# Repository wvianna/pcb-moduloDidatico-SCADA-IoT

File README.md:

# Projeto: PCB Módulo Didático SCADA/IoT

## Descrição do Projeto
Este projeto tem como objetivo fornecer uma plataforma de aprendizado para estudantes e entusiastas de automação industrial, sistemas SCADA e Internet das Coisas (IoT). A placa de circuito impresso (PCB) foi projetada para ser utilizada em laboratórios educacionais, permitindo a prática de conceitos teóricos em um ambiente controlado.

A PCB integra um **NodeMCU v2 (ESP8266)** com os seguintes componentes onboard:

- **Potenciômetro** — sinal analógico variável (simula sensor analógico)
- **Sensor DS18B20** — temperatura digital via 1-Wire
- **Driver de potência (transistor/resistência de aquecimento)** — carga controlada por PWM
- **Driver para servomotores** — canais PWM para azimute e elevação
- **Interface RS485 (MAX485)** — comunicação serial industrial half-duplex
- **Conectores para coils** — saídas digitais para relés ou buzzer
- **Conectores para entradas digitais** — contato seco ou switch onboard
- **LEDs de sinalização** — indicação visual de estado

---

> 🧩 **Projeto do firmware:** Este projeto foi desenvolvido para o firmware disponível em [github.com/wvianna/pcb-moduloDidatico-SCADA-IoT-firmware](https://github.com/wvianna/pcb-moduloDidatico-SCADA-IoT-firmware). O firmware gerencia todos os I/Os, sensores e interface RS485, implementando comunicação via **Modbus TCP/RTU**, **MQTT** e **OPC UA PubSub** — com seleção de protocolo via interface web.

---

**Autor:** William da Silva Vianna  
**Software Utilizado:** KiCad (v9 ou superior)

---

## 🧠 Visão Geral da Arquitetura

```mermaid
flowchart LR
  subgraph PCB["Placa PCB (Hardware)"]
    direction TB
    NODE[NodeMCU ESP8266]
    SEN[Sensores<br/>ADC + DS18B20]
    ATU[Atuadores<br/>Coils + PWM + Resistência]
    RS[RS485 MAX485]
    IN[Entradas Digitais]
  end

  subgraph FW["Firmware (software)"]
    REG[Modelo Interno<br/>de Registradores]
    PROT[Protocolo Ativo<br/>Modbus / MQTT / OPC UA]
    WEB[Servidor Web<br/>de Configuração]
  end

  subgraph EXT["Mundo Externo"]
    SCADA[SCADA / IHM]
    BRK[Broker MQTT]
    NRED[Node-RED]
  end

  NODE --> REG
  SEN --> REG
  REG --> ATU
  REG --> IN
  REG --> PROT
  WEB --> REG
  PROT --> SCADA
  PROT --> BRK
  PROT --> NRED
  RS -.-> SCADA
```

---

## � Pinout do NodeMCU

A imagem abaixo mostra a numeração dos pinos do **NodeMCU v2 (ESP8266)** utilizada no projeto. 

---

## �📋 Mapeamento de I/Os Físicos

A tabela abaixo relaciona cada funcionalidade da PCB ao pino do NodeMCU e ao registro Modbus correspondente. Este mapeamento é idêntico para todos os protocolos (Modbus, MQTT e OPC UA).

### Saídas Discretas (Coils)

| Endereço Modbus | Função | Pino NodeMCU | GPIO | Componente na PCB |
| ---: | --- | --- | --- | --- |
| 00001 | Saída discreta 1 | D0 | GPIO16 | Conector para relé/buzzer |
| 00002 | Saída discreta 2 | TX | GPIO1 | Conector para relé/buzzer |

### Entradas Discretas (Discrete Inputs)

| Endereço Modbus | Função | Pino NodeMCU | GPIO | Componente na PCB |
| ---: | --- | --- | --- | --- |
| 10001 | Entrada discreta 1 | D8 | GPIO15 | Switch onboard ou contato seco externo |
| 10002 | Entrada discreta 2 | RX | GPIO3 | Switch onboard ou contato seco externo |

> **Nota:** A entrada discreta 1 (ED1 / D8) também funciona como *boot pin* para forçar o modo de setup — basta colocá-la em nível baixo e reiniciar a placa.

### Entradas Analógicas (Input Registers)

| Endereço Modbus | Função | Pino NodeMCU | Faixa | Componente na PCB |
| ---: | --- | --- | ---: | --- |
| 30001 | ADC (potenciômetro) | A0 | 0..1023 | Potenciômetro onboard |
| 30002 | DS18B20 (temperatura) | D2 / GPIO4 | 0..1250 (x10 °C) | Sensor DS18B20 onboard |

### Saídas PWM (Holding Registers)

| Endereço Modbus | Função | Pino NodeMCU | GPIO | Faixa | Componente na PCB |
| ---: | --- | --- | --- | ---: | --- |
| 40001 | PWM azimute | D7 | GPIO13 | 0..1023 | Driver para servomotor |
| 40002 | PWM elevação | D3 | GPIO0 | 0..1023 | Driver para servomotor |
| 40003 | PWM resistência de aquecimento | D1 | GPIO5 | 0..1023 | Transistor + resistor de aquecimento onboard |

### Interface RS485 (Modbus RTU)

| Sinal MAX485 | Pino NodeMCU | GPIO |
| --- | --- | --- |
| RO (receptor) | D5 | GPIO14 |
| DI (driver) | D6 | GPIO12 |
| DE + RE (direção) | D4 | GPIO2 |

---
TIPO       |     DEVICE     | RANGE  |MODBUS
SD1        |BUZZER - PONTE H| 0 1    |COIL 00001
SD2        |RELE - PONTE H  | 0 1    |COIL 00002
PWM1       |SERVO - AZIMUTE | 0~1023 |H.R. 40001
PWM2       |SERVO - ELEVAÇÃO| 0~1023 |H.R. 40002
PMW3       |RESISTÊNCIA     | 0~1023 |H.R. 40003
ED1        |SW SECO - SETUP | 0 1    |D.I. 10001
ED2        |SW SECO         | 0 1    |D.I. 10002
EA0        |POTENCIÔMETRO   | 0~1023 |I.R. 30001
TEMPERATURA|DS18B20         | oC X 10|I.R. 30002
---

## 🔌 Diagrama de Blocos da PCB

```mermaid
flowchart TD
  subgraph PCB["PCB Módulo Didático SCADA/IoT"]
    MCU[NodeMCU ESP8266]

    subgraph ENTRADAS["Entradas"]
      POTE[Potenciômetro<br/>A0 / ADC]
      DS18[DS18B20<br/>D2 / 1-Wire]
      SW1[Switch ED1<br/>D8 / GPIO15]
      SW2[Switch ED2<br/>RX / GPIO3]
    end

    subgraph SAIDAS["Saídas"]
      C1[Coil 1<br/>D0 / GPIO16]
      C2[Coil 2<br/>TX / GPIO1]
      SRV1[Servo Azimute<br/>D7 / PWM]
      SRV2[Servo Elevação<br/>D3 / PWM]
      AQUE[Resistência<br/>D1 / PWM]
    end

    subgraph COMUM["Comunicação"]
      RS485[MAX485<br/>RS485 Half-Duplex]
    end

    subgraph SINAL["Sinalização"]
      LED[LED Config<br/>D4 / GPIO2]
    end

    MCU --- ENTRADAS
    MCU --- SAIDAS
    MCU --- RS485
    MCU --- SINAL
  end
```

---

## ⚡ Especificações Elétricas

| Parâmetro | Valor |
| --- | --- |
| Alimentação da placa | 5V DC (via USB ou conector) |
| Regulador onboard | 3,3V para o NodeMCU |
| Nível lógico dos GPIOs | 3,3V |
| Corrente máxima por GPIO | ~12 mA (com resistor de limitação) |
| Tensão no barramento RS485 | Diferencial (A/B) |
| Temperatura do DS18B20 | -55°C a +125°C |
| Faixa do ADC | 0..3,3V (10 bits, 0..1023) |

---

## 💻 Necessidade de Firmware

> ⚠️ **Nota Importante:** Este hardware **não é puramente analógico**. A placa foi projetada ao redor de uma arquitetura programável — o circuito impresso isolado não desempenha nenhuma função sem o respectivo **firmware**.

O firmware disponível em [pcb-moduloDidatico-SCADA-IoT-firmware](https://github.com/wvianna/pcb-moduloDidatico-SCADA-IoT-firmware) implementa:

1. **Inicialização (Setup):** Configuração dos registradores, direção dos pinos de I/O e taxas de transmissão dos barramentos.
2. **Loop principal cooperativo:** Leitura cíclica de sensores, atualização do modelo interno de registradores e aplicação nas saídas físicas — sem uso de `delay()` bloqueante.
3. **Servidor web de configuração:** Interface para definir SSID, IP, protocolo ativo (Modbus/MQTT/OPC UA) e parâmetros de comunicação, acessível via modo AP.
4. **Pilhas de comunicação:** Modbus TCP (porta 502), Modbus RTU (RS485), MQTT (PubSubClient) e OPC UA PubSub sobre MQTT.
5. **Persistência em LittleFS:** Configuração salva em arquivo texto na flash, com validação e fallback para valores padrão.

---

## 📁 Estrutura de Arquivos no Repositório

```text
├── esquema.pdf             # Diagrama esquemático exportado para leitura
├── meu-projeto.kicad_pro   # Arquivo de gerenciamento do projeto KiCad
├── meu-projeto.kicad_sch   # Folha do desenho esquemático
├── meu-projeto.kicad_pcb   # Layout da placa de circuito impresso
├── docs/
│   ├── mapeamentopinosmb.txt  # Mapa de pinos em formato CSV
│   └── requisitos.txt         # Requisitos elétricos e funcionais
├── firmware/                  # Submódulo do firmware
└── .gitignore              # Filtro de arquivos temporários do KiCad
```

---

## 🔗 Links Relacionados

| Recurso | Link |
| --- | --- |
| Repositório do firmware | [github.com/wvianna/pcb-moduloDidatico-SCADA-IoT-firmware](https://github.com/wvianna/pcb-moduloDidatico-SCADA-IoT-firmware) |
| Documentação do firmware | README do firmware |
| Esquema elétrico | `esquema.pdf` neste repositório |
| Mapa de pinos (CSV) | `docs/mapeamentopinosmb.txt` |

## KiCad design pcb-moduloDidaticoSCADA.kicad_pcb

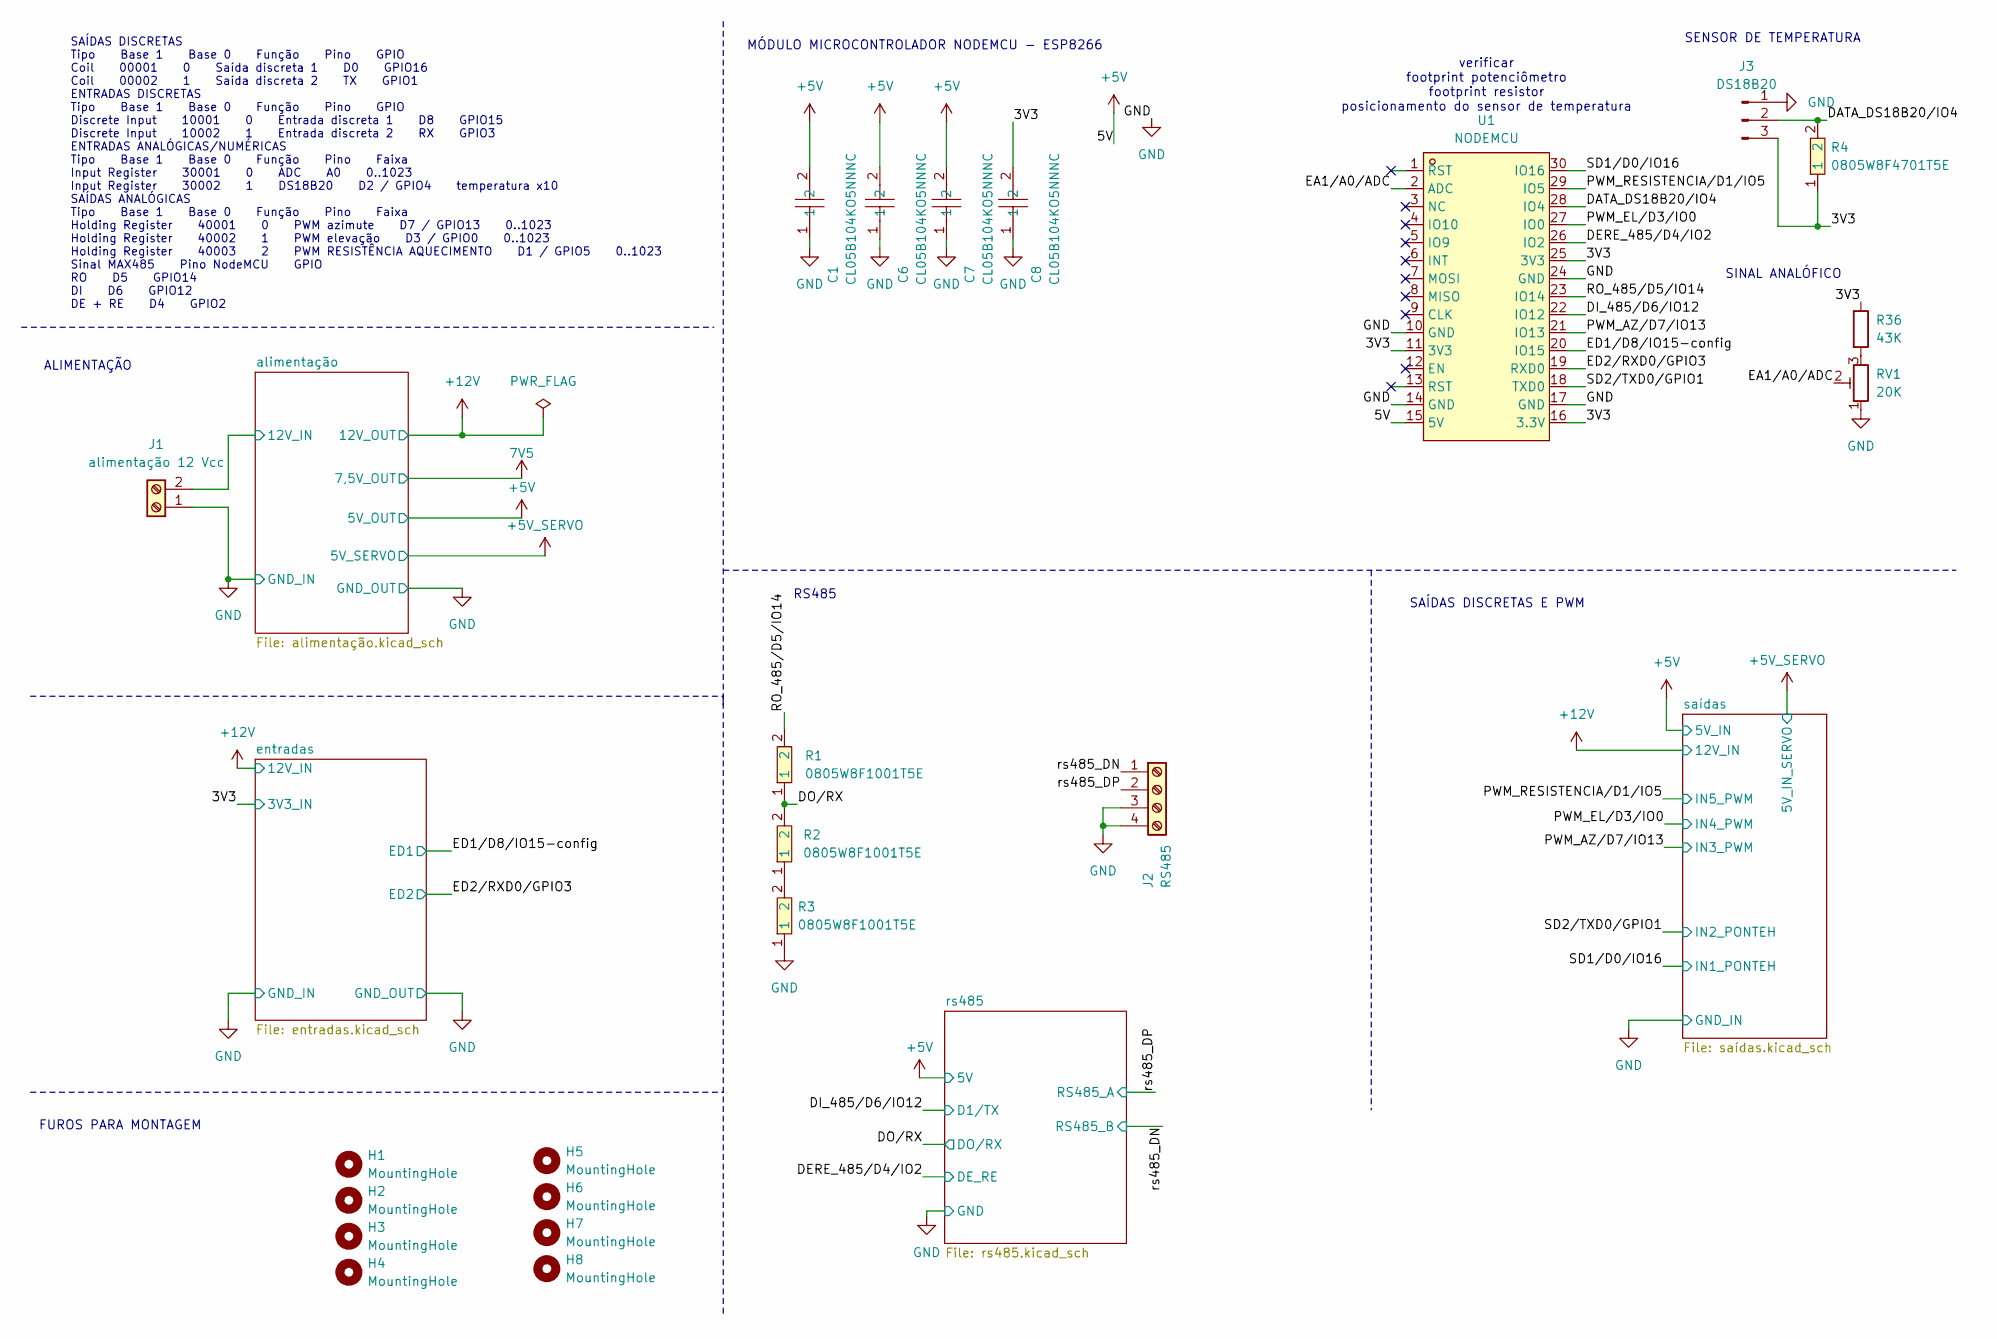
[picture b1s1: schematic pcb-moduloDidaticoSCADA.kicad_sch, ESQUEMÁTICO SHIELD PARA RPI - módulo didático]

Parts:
C1, C6, C7, C8: CL05B104KO5NNNC; C0402; MPN CL05B104KO5NNNC; LCSC Part C1525
H1, H2, H3, H4, H5, H6, H7, H8: MountingHole; MountingHole_3.2mm_M3
J1: alimentação 12 Vcc; TerminalBlock_MaiXu_MX126-5.0-02P_1x02_P5.00mm
J2: RS485; TerminalBlock_MetzConnect_Type101_RT01604HBWC_1x04_P5.08mm_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
J3: DS18B20; PinSocket_1x03_P2.54mm_Vertical
R1, R2, R3: 0805W8F1001T5E; R0805; MPN 0805W8F1001T5E; LCSC Part C17513
R4: 0805W8F4701T5E; R0805; LCSC Part C17673
R36: 43K; R_0805_2012Metric_Pad1.20x1.40mm_HandSolder
RV1: 20K; Potentiometer_Alpha_RD901F-40-00D_Single_Vertical
U1: NODEMCU; COMM-TH_NODEMCU-12F; MPN NODEMCU(12F); LCSC Part C2764098

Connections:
+5V: C1.2, C6.2, C7.2, U1.15 (5V); also elsewhere on the board
+12V: J1.2; also elsewhere on the board
/3V3: C8.2, J3.3, R4.1, R36.1, U1.11 (3V3), U1.16 (3.3V), U1.25 (3V3); also elsewhere on the board
/DATA_DS18B20/IO4: J3.2, R4.2, U1.28 (IO4)
/DERE_485/D4/IO2: U1.26 (IO2); also elsewhere on the board
/DI_485/D6/IO12: U1.22 (IO12); also elsewhere on the board
/DO/RX: R1.1, R2.2; also elsewhere on the board
/EA1/A0/ADC: RV1.2, U1.2 (ADC)
/ED1/D8/IO15-config: U1.20 (IO15); also elsewhere on the board
/ED2/RXD0/GPIO3: U1.19 (RXD0); also elsewhere on the board
/PWM_AZ/D7/IO13: U1.21 (IO13); also elsewhere on the board
/PWM_EL/D3/IO0: U1.27 (IO0); also elsewhere on the board
/PWM_RESISTENCIA/D1/IO5: U1.29 (IO5); also elsewhere on the board
/RO_485/D5/IO14: R1.2, U1.23 (IO14)
/SD1/D0/IO16: U1.30 (IO16); also elsewhere on the board
/SD2/TXD0/GPIO1: U1.18 (TXD0); also elsewhere on the board
/rs485_DN: J2.1; also elsewhere on the board
/rs485_DP: J2.2; also elsewhere on the board
GND: C1.1, C6.1, C7.1, C8.1, J1.1, J2.3, J2.4, J3.1, R3.1, RV1.1, U1.10 (GND), U1.14 (GND), U1.17 (GND), U1.24 (GND); also elsewhere on the board
unnamed: R2.1, R3.2
unnamed: R36.2, RV1.3

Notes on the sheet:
SENSOR DE TEMPERATURA
MÓDULO MICROCONTROLADOR NODEMCU - ESP8266
FUROS PARA MONTAGEM
SINAL ANALÓFICO
verificar footprint potenciômetro footprint resistor posicionamento do sensor de temperatura
ALIMENTAÇÃO
SAÍDAS DISCRETAS E PWM
RS485
SAÍDAS DISCRETAS Tipo Base 1 Base 0 Função Pino GPIO Coil 00001 0 Saída discreta 1 D0 GPIO16 Coil 00002 1 Saída discreta 2 TX GPIO1 ENTRADAS DISCRETAS Tipo Base 1 Base 0 Função Pino GPIO Discrete Input 10001 0 Entrada discreta 1 D8 GPIO15 Discrete Input 10002 1 Entrada discreta 2 RX GPIO3 ENTRADAS 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

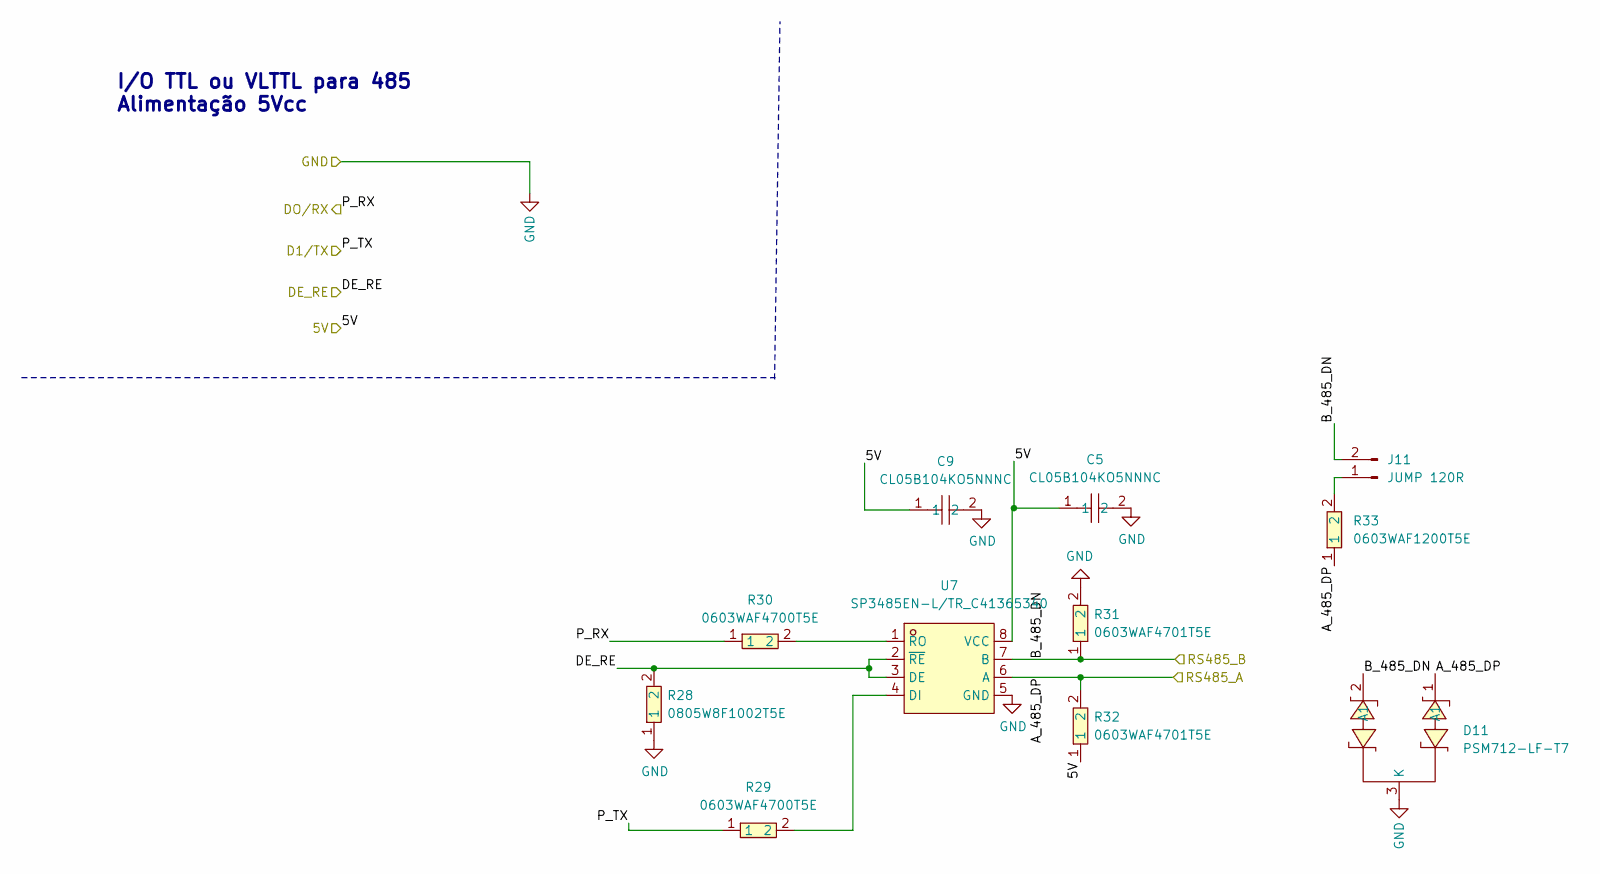
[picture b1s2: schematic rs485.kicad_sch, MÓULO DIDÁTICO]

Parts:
C5, C9: CL05B104KO5NNNC; C0402; MPN CL05B104KO5NNNC; LCSC Part C1525
D11: PSM712-LF-T7; SOT-23-3_L3.0-W1.7-P0.95-LS2.9-BR; MPN PSM712-LF-T7; LCSC Part C32677
J11: JUMP 120R; PinSocket_1x02_P2.54mm_Vertical
R28: 0805W8F1002T5E; R0805; MPN 0805W8F1002T5E; LCSC Part C17414
R29, R30: 0603WAF4700T5E; R0603; MPN 0603WAF4700T5E; LCSC Part C23179
R31, R32: 0603WAF4701T5E; R0603; MPN 0603WAF4701T5E; LCSC Part C23162
R33: 0603WAF1200T5E; R0603; MPN 0603WAF1200T5E; LCSC Part C22787
U7: SP3485EN-L/TR_C41365340; SO-8_L4.9-W3.9-P1.27-LS6.0-BL; MPN SP3485EN-L/TR; LCSC Part C41365340

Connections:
+5V: C5.1, C9.1, R32.1, U7.8 (VCC); also elsewhere on the board
/DERE_485/D4/IO2: R28.2, U7.2 (~RE), U7.3 (DE); also elsewhere on the board
/DI_485/D6/IO12: R29.1; also elsewhere on the board
/DO/RX: R30.1; also elsewhere on the board
/rs485_DN: D11.2 (A1), J11.2, R31.1, U7.7 (B); also elsewhere on the board
/rs485_DP: D11.1 (A1), R32.2, R33.1, U7.6 (A); also elsewhere on the board
GND: C5.2, C9.2, D11.3 (K), R28.1, R31.2, U7.5 (GND); also elsewhere on the board
unnamed: J11.1, R33.2
unnamed: R29.2, U7.4 (DI)
unnamed: R30.2, U7.1 (RO)

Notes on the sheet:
I/O TTL ou VLTTL para 485 Alimentação 5Vcc

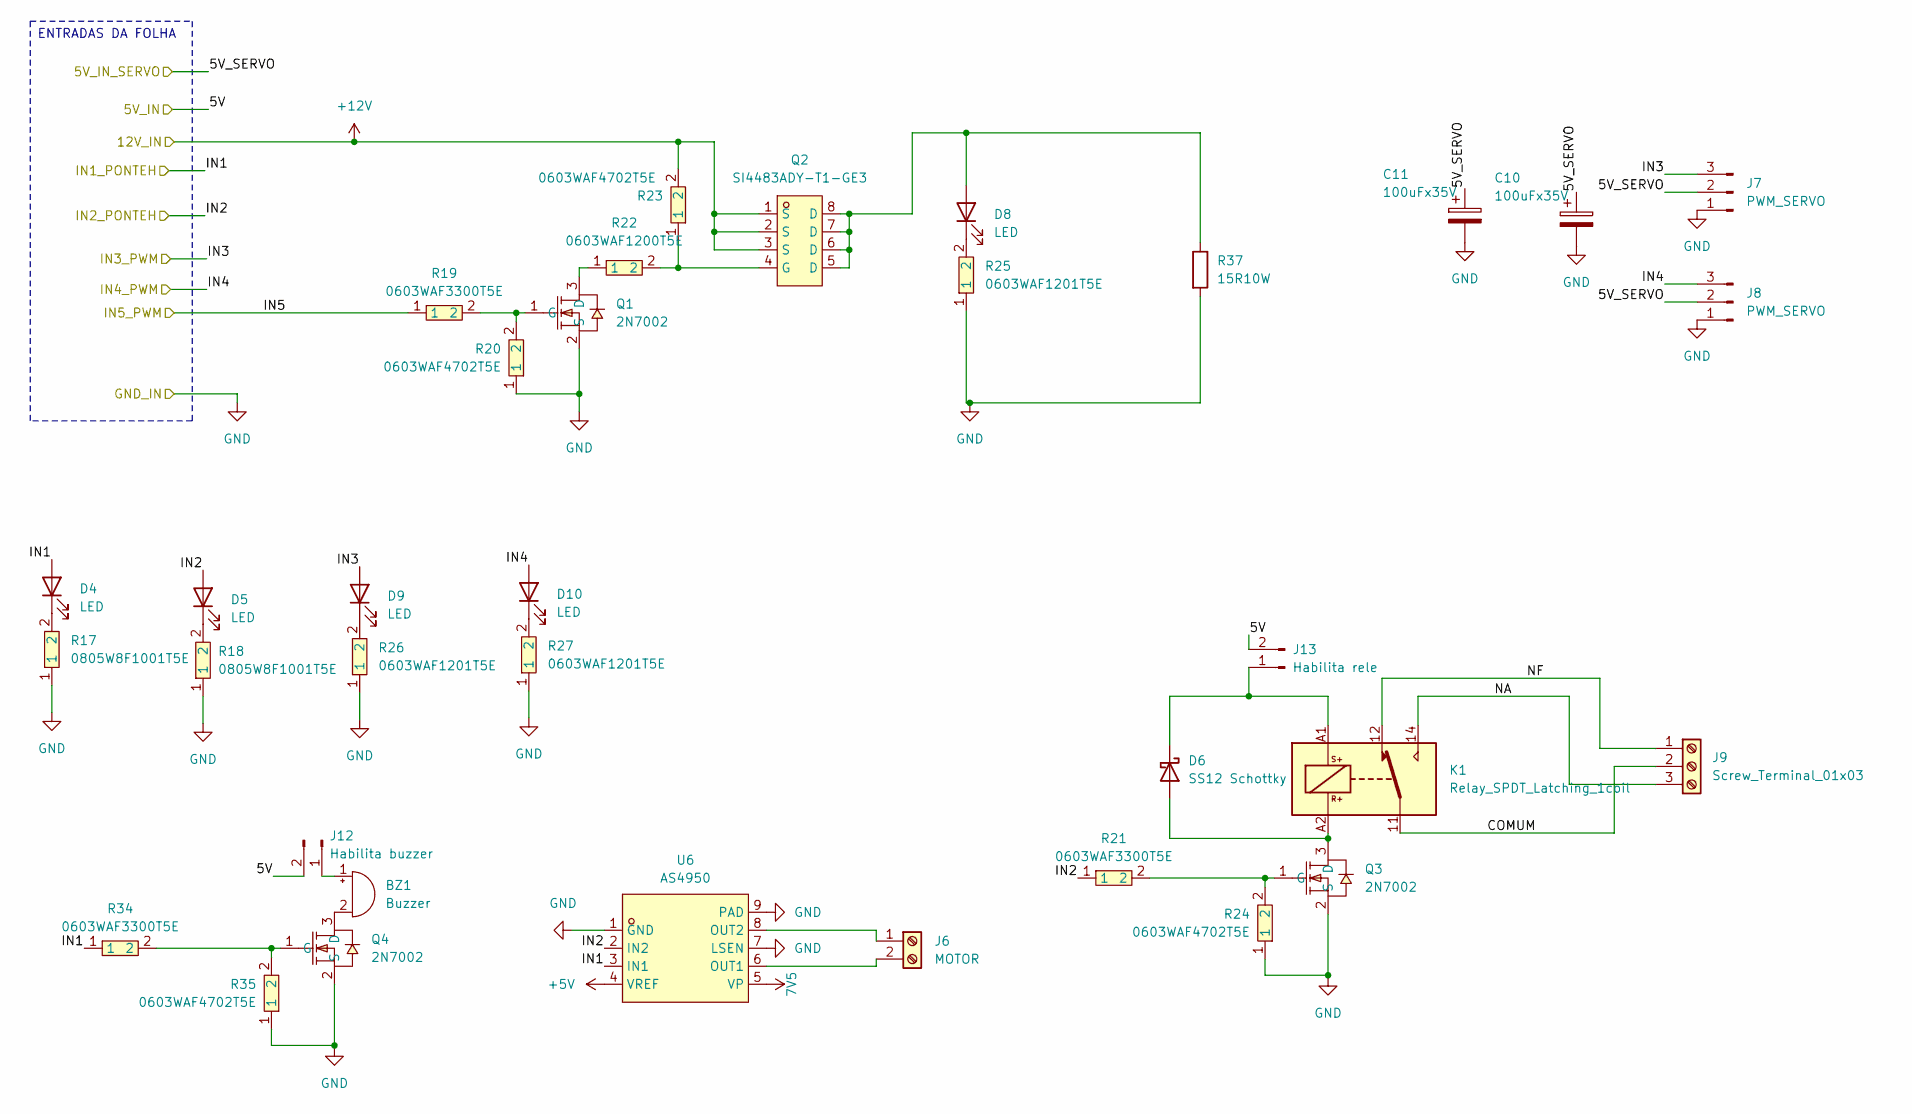
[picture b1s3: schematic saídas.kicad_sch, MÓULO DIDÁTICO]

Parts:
BZ1: Buzzer; Buzzer_12x9.5RM7.6
C10, C11: 100uFx35V; CP_Radial_D8.0mm_P3.50mm
D4, D5, D8, D9, D10: LED; LED_D5.0mm
D6: SS12 Schottky; D_SMA_Handsoldering
J6: MOTOR; TerminalBlock_MaiXu_MX126-5.0-02P_1x02_P5.00mm
J7, J8: PWM_SERVO; PinSocket_1x03_P2.54mm_Vertical
J9: Screw_Terminal_01x03; TerminalBlock_RND_205-00288_1x03_P5.08mm_Horizontal
J12: Habilita buzzer; PinSocket_1x02_P2.54mm_Vertical
J13: Habilita rele; PinSocket_1x02_P2.54mm_Vertical
K1: Relay_SPDT_Latching_1coil; Relay_SPDT_Finder_36.11
Q1, Q3, Q4: 2N7002; SOT-23-3_L2.9-W1.3-P1.90-LS2.4-BR; MPN 2N7002; LCSC Part C8545
Q2: SI4483ADY-T1-GE3; SO-8_L4.9-W3.9-P1.27-LS6.0-BL; LCSC Part C727843
R17, R18: 0805W8F1001T5E; R0805; MPN 0805W8F1001T5E; LCSC Part C17513
R19, R21, R34: 0603WAF3300T5E; R0603; MPN 0603WAF3300T5E; LCSC Part C23138
R20, R23, R24, R35: 0603WAF4702T5E; R0603; MPN 0603WAF4702T5E; LCSC Part C25819
R22: 0603WAF1200T5E; R0603; MPN 0603WAF1200T5E; LCSC Part C22787
R25, R26, R27: 0603WAF1201T5E; R0603; MPN 0603WAF1201T5E; LCSC Part C22765
R37: 15R10W; R_Axial_Power_L38.0mm_W9.0mm_P40.64mm
U6: AS4950; ESOP-8_L4.9-W3.9-P1.27-LS6.0-BL-EP; MPN AS4950; LCSC Part C2929412

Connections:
7V5: U6.5 (VP); also elsewhere on the board
+5V: J12.2, J13.2, U6.4 (VREF); also elsewhere on the board
+5V_SERVO: C10.1, C11.1, J7.2, J8.2; also elsewhere on the board
+12V: Q2.1 (S), Q2.2 (S), Q2.3 (S), R23.2; also elsewhere on the board
/PWM_AZ/D7/IO13: D9.2 (A), J7.3; also elsewhere on the board
/PWM_EL/D3/IO0: D10.2 (A), J8.3; also elsewhere on the board
/PWM_RESISTENCIA/D1/IO5: R19.1; also elsewhere on the board
/SD1/D0/IO16: D4.2 (A), R34.1, U6.3 (IN1); also elsewhere on the board
/SD2/TXD0/GPIO1: D5.2 (A), R21.1, U6.2 (IN2); also elsewhere on the board
/saídas/COMUM: J9.2, K1.11
/saídas/NA: J9.3, K1.14
/saídas/NF: J9.1, K1.12
GND: C10.2, C11.2, J7.1, J8.1, Q1.2 (S), Q3.2 (S), Q4.2 (S), R17.1, R18.1, R20.1, R24.1, R25.1, R26.1, R27.1, R35.1, R37.2, U6.1 (GND), U6.7 (LSEN), U6.9 (PAD); also elsewhere on the board
unnamed: BZ1.1 (+), J12.1
unnamed: BZ1.2 (-), Q4.3 (D)
unnamed: D4.1 (K), R17.2
unnamed: D5.1 (K), R18.2
unnamed: D6.2 (A), K1.A2, Q3.3 (D)
unnamed: D6.1 (K), J13.1, K1.A1
unnamed: D8.2 (A), Q2.5 (D), Q2.6 (D), Q2.7 (D), Q2.8 (D), R37.1
unnamed: D8.1 (K), R25.2
unnamed: D9.1 (K), R26.2
unnamed: D10.1 (K), R27.2
unnamed: J6.1, U6.8 (OUT2)
unnamed: J6.2, U6.6 (OUT1)
unnamed: Q1.3 (D), R22.1
unnamed: Q1.1 (G), R19.2, R20.2
unnamed: Q2.4 (G), R22.2, R23.1
unnamed: Q3.1 (G), R21.2, R24.2
unnamed: Q4.1 (G), R34.2, R35.2

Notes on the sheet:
ENTRADAS DA FOLHA

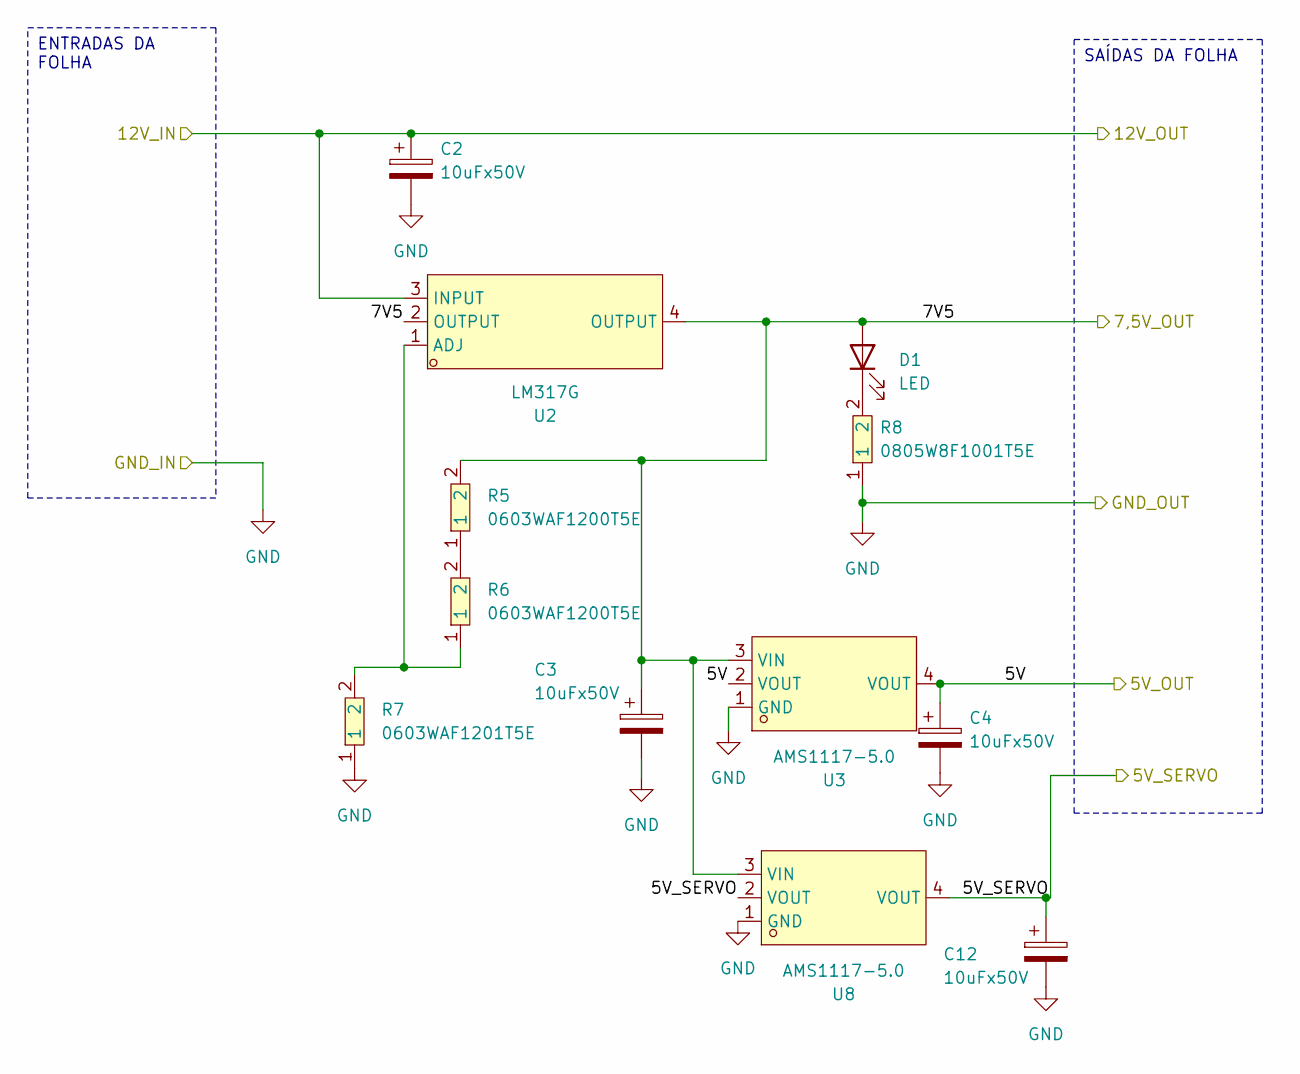
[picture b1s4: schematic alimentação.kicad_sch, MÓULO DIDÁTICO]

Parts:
C2, C3, C4, C12: 10uFx50V; CP_Radial_D5.0mm_P2.50mm
D1: LED; LED_D5.0mm
R5, R6: 0603WAF1200T5E; R0603; MPN 0603WAF1200T5E; LCSC Part C22787
R7: 0603WAF1201T5E; R0603; MPN 0603WAF1201T5E; LCSC Part C22765
R8: 0805W8F1001T5E; R0805; MPN 0805W8F1001T5E; LCSC Part C17513
U2: LM317G; SOT-223_L6.5-W3.5-P2.30-LS7.0-BR; MPN LM317G; LCSC Part C347367
U3, U8: AMS1117-5.0; SOT-223_L6.5-W3.5-P2.30-LS7.0-BR; MPN AMS1117-5.0; LCSC Part C6187

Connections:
7V5: C3.1, D1.2 (A), R5.2, U2.2 (OUTPUT), U2.4 (OUTPUT), U3.3 (VIN), U8.3 (VIN); also elsewhere on the board
+5V: C4.1, U3.2 (VOUT), U3.4 (VOUT); also elsewhere on the board
+5V_SERVO: C12.1, U8.2 (VOUT), U8.4 (VOUT); also elsewhere on the board
+12V: C2.1, U2.3 (INPUT); also elsewhere on the board
GND: C2.2, C3.2, C4.2, C12.2, R7.1, R8.1, U3.1 (GND), U8.1 (GND); also elsewhere on the board
unnamed: D1.1 (K), R8.2
unnamed: R5.1, R6.2
unnamed: R6.1, R7.2, U2.1 (ADJ)

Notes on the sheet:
ENTRADAS DA FOLHA
SAÍDAS DA FOLHA

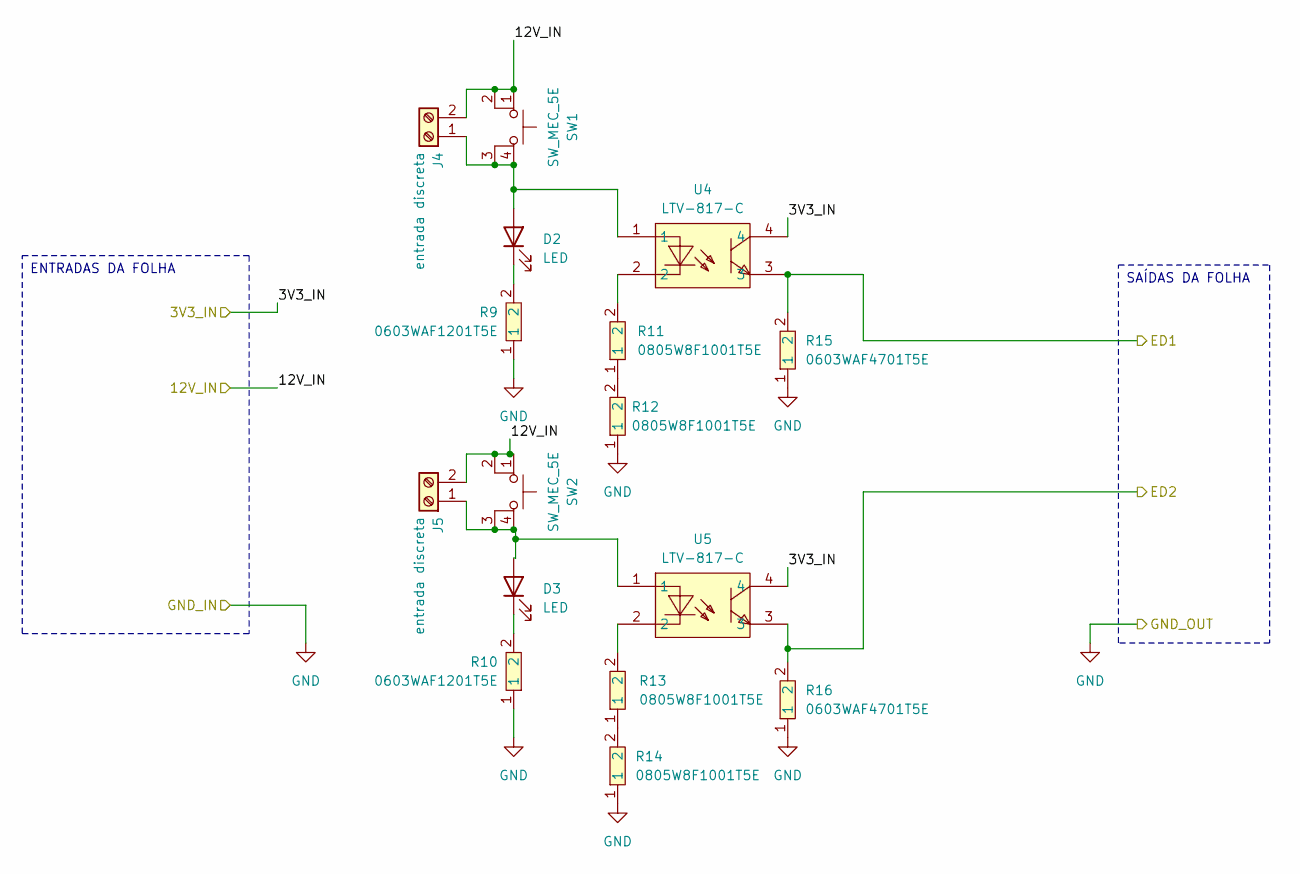
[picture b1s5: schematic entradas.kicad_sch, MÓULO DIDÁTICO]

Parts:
D2, D3: LED; LED_D5.0mm
J4, J5: entrada discreta; TerminalBlock_MaiXu_MX126-5.0-02P_1x02_P5.00mm
R9, R10: 0603WAF1201T5E; R0603; MPN 0603WAF1201T5E; LCSC Part C22765
R11, R12, R13, R14: 0805W8F1001T5E; R0805; MPN 0805W8F1001T5E; LCSC Part C17513
R15, R16: 0603WAF4701T5E; R0603; MPN 0603WAF4701T5E; LCSC Part C23162
SW1, SW2: SW_MEC_5E; SW_MEC_5GSH9
U4, U5: LTV-817-C; DIP-4_L4.6-W6.5-P2.54-LS7.6-BL

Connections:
+12V: J4.2, J5.2, SW1.1, SW1.2, SW2.1, SW2.2; also elsewhere on the board
/3V3: U4.4, U5.4; also elsewhere on the board
/ED1/D8/IO15-config: R15.2, U4.3; also elsewhere on the board
/ED2/RXD0/GPIO3: R16.2, U5.3; also elsewhere on the board
GND: R9.1, R10.1, R12.1, R14.1, R15.1, R16.1; also elsewhere on the board
unnamed: D2.2 (A), J4.1, SW1.3 (K), SW1.4 (A), U4.1
unnamed: D2.1 (K), R9.2
unnamed: D3.2 (A), J5.1, SW2.3 (K), SW2.4 (A), U5.1
unnamed: D3.1 (K), R10.2
unnamed: R11.1, R12.2
unnamed: R11.2, U4.2
unnamed: R13.1, R14.2
unnamed: R13.2, U5.2

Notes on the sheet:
ENTRADAS DA FOLHA
SAÍDAS DA FOLHA

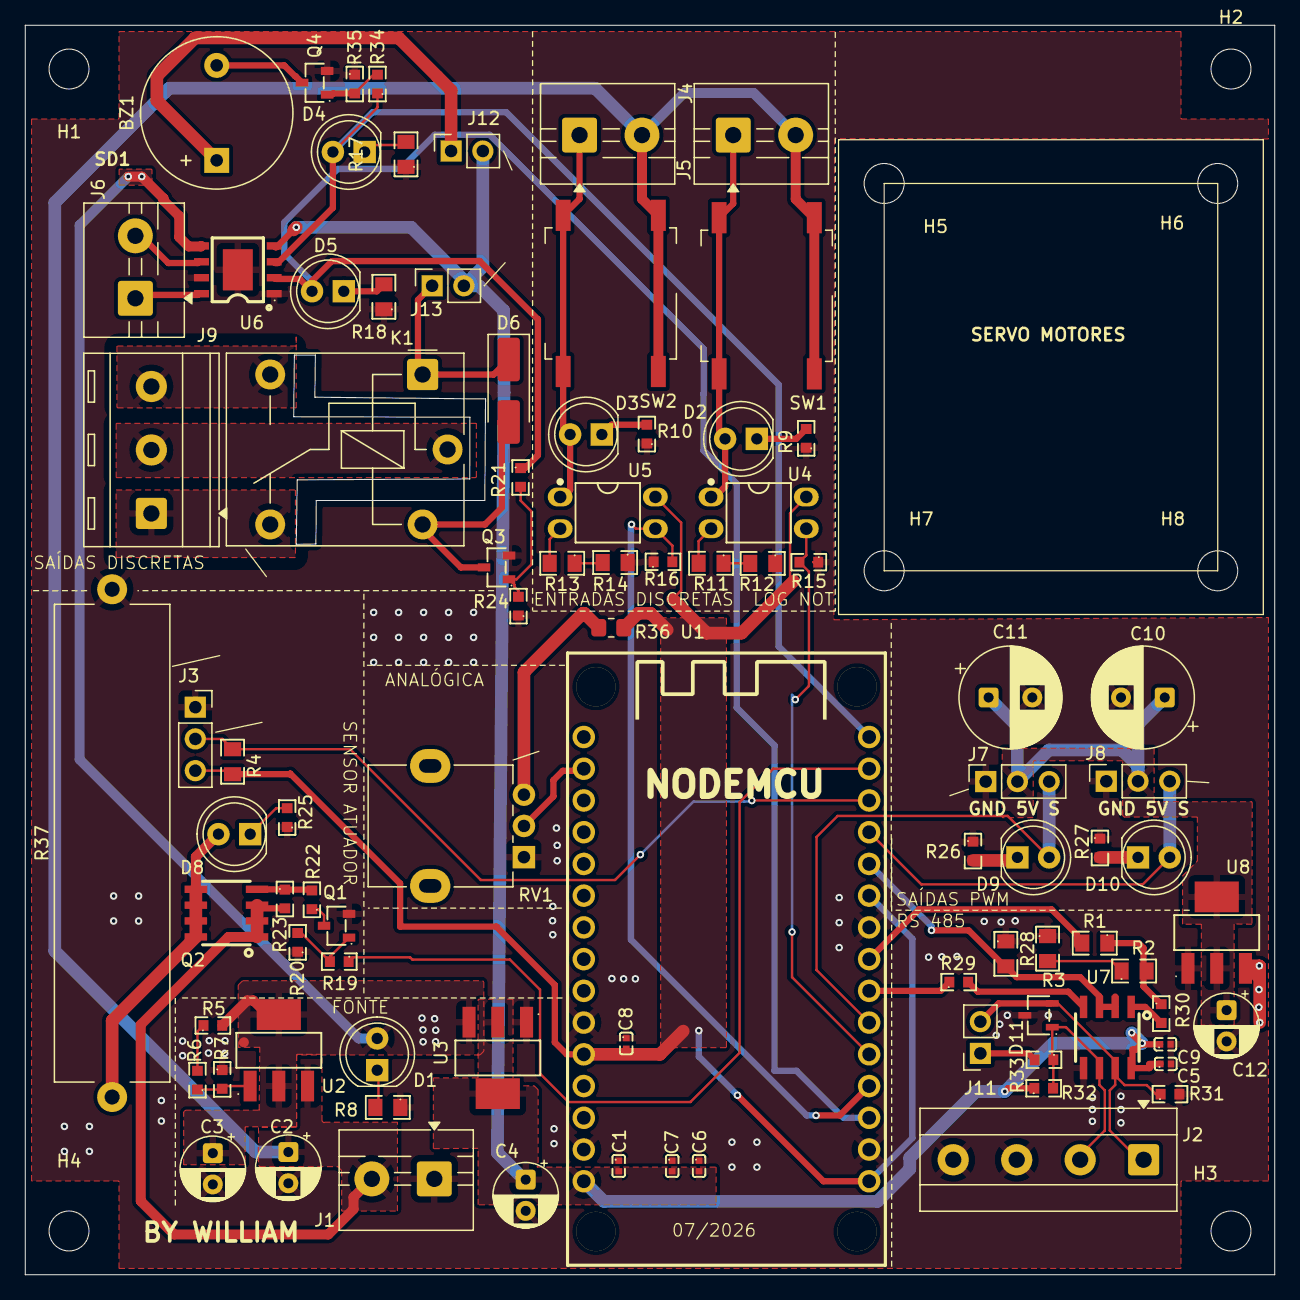
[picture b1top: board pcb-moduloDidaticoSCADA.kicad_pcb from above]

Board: 2 copper layers, 100.0 x 100.0 mm, 96 parts (0 on the bottom side), 57 nets.
